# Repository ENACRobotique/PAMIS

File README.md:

# PAMIS_202

Limiter le courant des stepper à 0.6 A

Enlever les solder bridges SB9 SB16 et SB18 de la nucleo L432KC

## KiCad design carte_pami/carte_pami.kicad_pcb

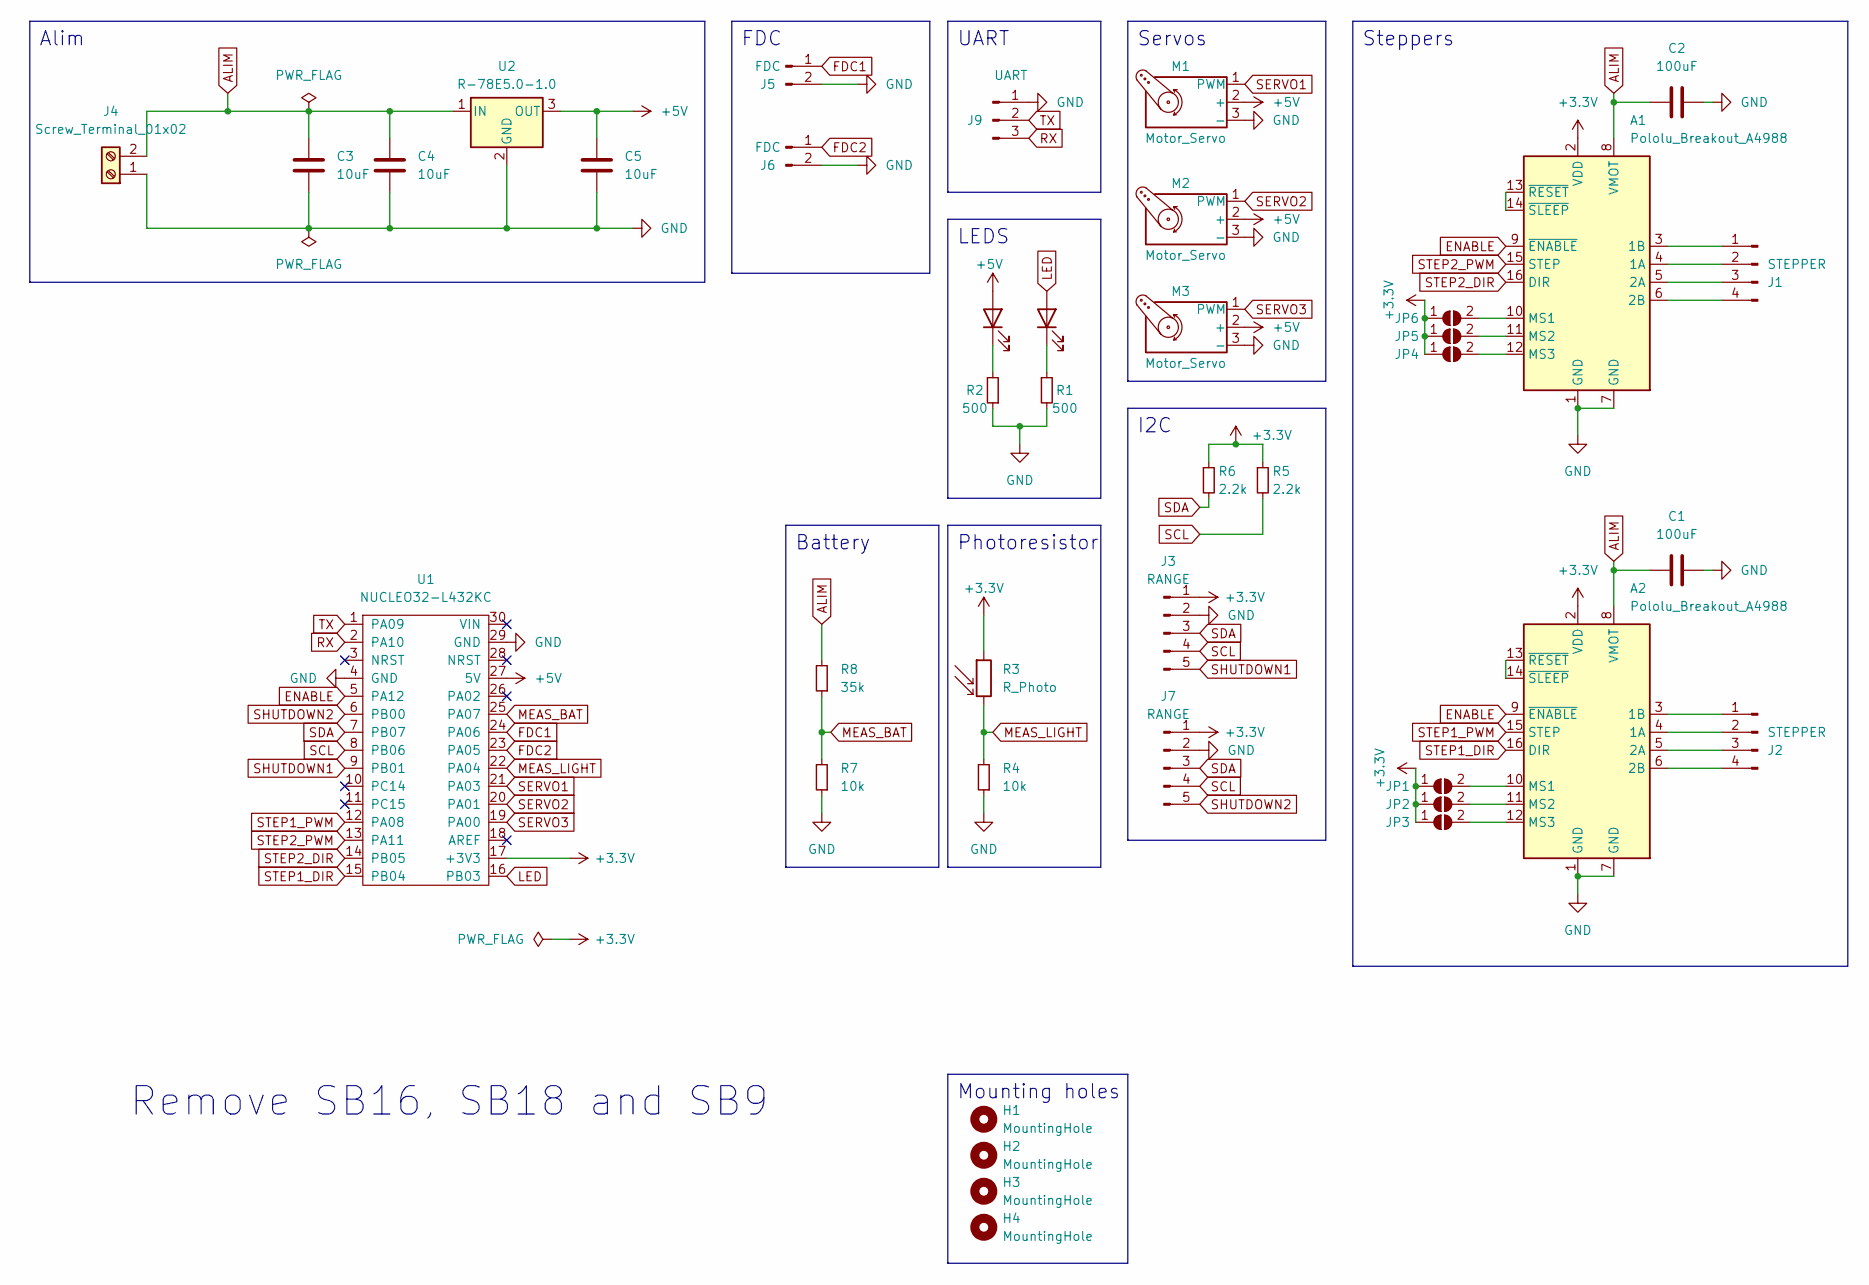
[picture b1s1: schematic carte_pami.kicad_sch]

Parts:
A1, A2: Pololu_Breakout_A4988; Pololu_Breakout-16_15.2x20.3mm
C1, C2: 100uF; CP_Elec_10x12.5
C3, C4, C5: 10uF; C_0805_2012Metric
D1, D2: LED; LED_0603_1608Metric
H1, H2, H3, H4: MountingHole; MountingHole_3.2mm_M3
J1, J2: STEPPER; PinHeader_1x04_P2.54mm_Vertical
J3, J7: RANGE; PinHeader_1x05_P2.54mm_Vertical
J4: Screw_Terminal_01x02; TerminalBlock_bornier-2_P5.08mm
J5, J6: FDC; PinHeader_1x02_P2.54mm_Vertical
J9: UART; PinHeader_1x03_P2.54mm_Vertical
JP1, JP2, JP3, JP4, JP5, JP6: SolderJumper_2_Open; SolderJumper-2_P1.3mm_Open_TrianglePad1.0x1.5mm
M1, M2, M3: Motor_Servo; PinHeader_1x03_P2.54mm_Vertical
R1, R2: 500; R_0805_2012Metric
R3: R_Photo; PinHeader_1x02_P2.54mm_Vertical
R4, R7: 10k; R_0805_2012Metric
R5, R6: 2.2k; R_0805_2012Metric
R8: 35k; R_0805_2012Metric
U1: NUCLEO32-L432KC; NUCLEO32
U2: R-78E5.0-1.0; Converter_DCDC_RECOM_R-78E-0.5_THT

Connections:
+3.3V: A1.2 (VDD), A2.2 (VDD), J3.1, J7.1, JP1.1 (A), JP2.1 (A), JP3.1 (A), JP4.1 (A), JP5.1 (A), JP6.1 (A), R3.1, R5.1, R6.1, U1.17 (+3V3)
+5V: C5.2, D1.2 (A), M1.2 (+), M2.2 (+), M3.2 (+), U1.27 (5V), U2.3 (OUT)
ALIM: A1.8 (VMOT), A2.8 (VMOT), C1.1, C2.1, C3.2, C4.2, J4.2, R8.2, U2.1 (IN)
ENABLE: A1.9 (~ENABLE), A2.9 (~ENABLE), U1.5 (PA12)
FDC1: J5.1, U1.24 (PA06)
FDC2: J6.1, U1.23 (PA05)
GND: A1.1 (GND), A1.7 (GND), A2.1 (GND), A2.7 (GND), C1.2, C2.2, C3.1, C4.1, C5.1, J3.2, J4.1, J5.2, J6.2, J7.2, J9.1, M1.3 (-), M2.3 (-), M3.3 (-), R1.2, R2.1, R4.1, R7.1, U1.4 (GND), U1.29 (GND), U2.2 (GND)
LED: D2.2 (A), U1.16 (PB03)
MEAS_BAT: R7.2, R8.1, U1.25 (PA07)
MEAS_LIGHT: R3.2, R4.2, U1.22 (PA04)
unnamed: A1.4 (1A), J1.2
unnamed: A1.3 (1B), J1.1
unnamed: A1.5 (2A), J1.3
unnamed: A1.6 (2B), J1.4
unnamed: A1.10 (MS1), JP6.2 (B)
unnamed: A1.11 (MS2), JP5.2 (B)
unnamed: A1.12 (MS3), JP4.2 (B)
unnamed: A1.13 (~RESET), A1.14 (~SLEEP)
unnamed: A2.4 (1A), J2.2
unnamed: A2.3 (1B), J2.1
unnamed: A2.5 (2A), J2.3
unnamed: A2.6 (2B), J2.4
unnamed: A2.10 (MS1), JP1.2 (B)
unnamed: A2.11 (MS2), JP2.2 (B)
unnamed: A2.12 (MS3), JP3.2 (B)
unnamed: A2.13 (~RESET), A2.14 (~SLEEP)
unnamed: D1.1 (K), R2.2
unnamed: D2.1 (K), R1.1
RX: J9.3, U1.2 (PA10)
SCL: J3.4, J7.4, R5.2, U1.8 (PB06)
SDA: J3.3, J7.3, R6.2, U1.7 (PB07)
SERVO1: M1.1 (PWM), U1.21 (PA03)
SERVO2: M2.1 (PWM), U1.20 (PA01)
SERVO3: M3.1 (PWM), U1.19 (PA00)
SHUTDOWN1: J3.5, U1.9 (PB01)
SHUTDOWN2: J7.5, U1.6 (PB00)
STEP1_DIR: A2.16 (DIR), U1.15 (PB04)
STEP1_PWM: A2.15 (STEP), U1.12 (PA08)
STEP2_DIR: A1.16 (DIR), U1.14 (PB05)
STEP2_PWM: A1.15 (STEP), U1.13 (PA11)
TX: J9.2, U1.1 (PA09)

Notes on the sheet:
Servos
UART
Photoresistor
Remove SB16, SB18 and SB9
LEDS
FDC
Steppers
I2C
Mounting holes
Alim
Battery

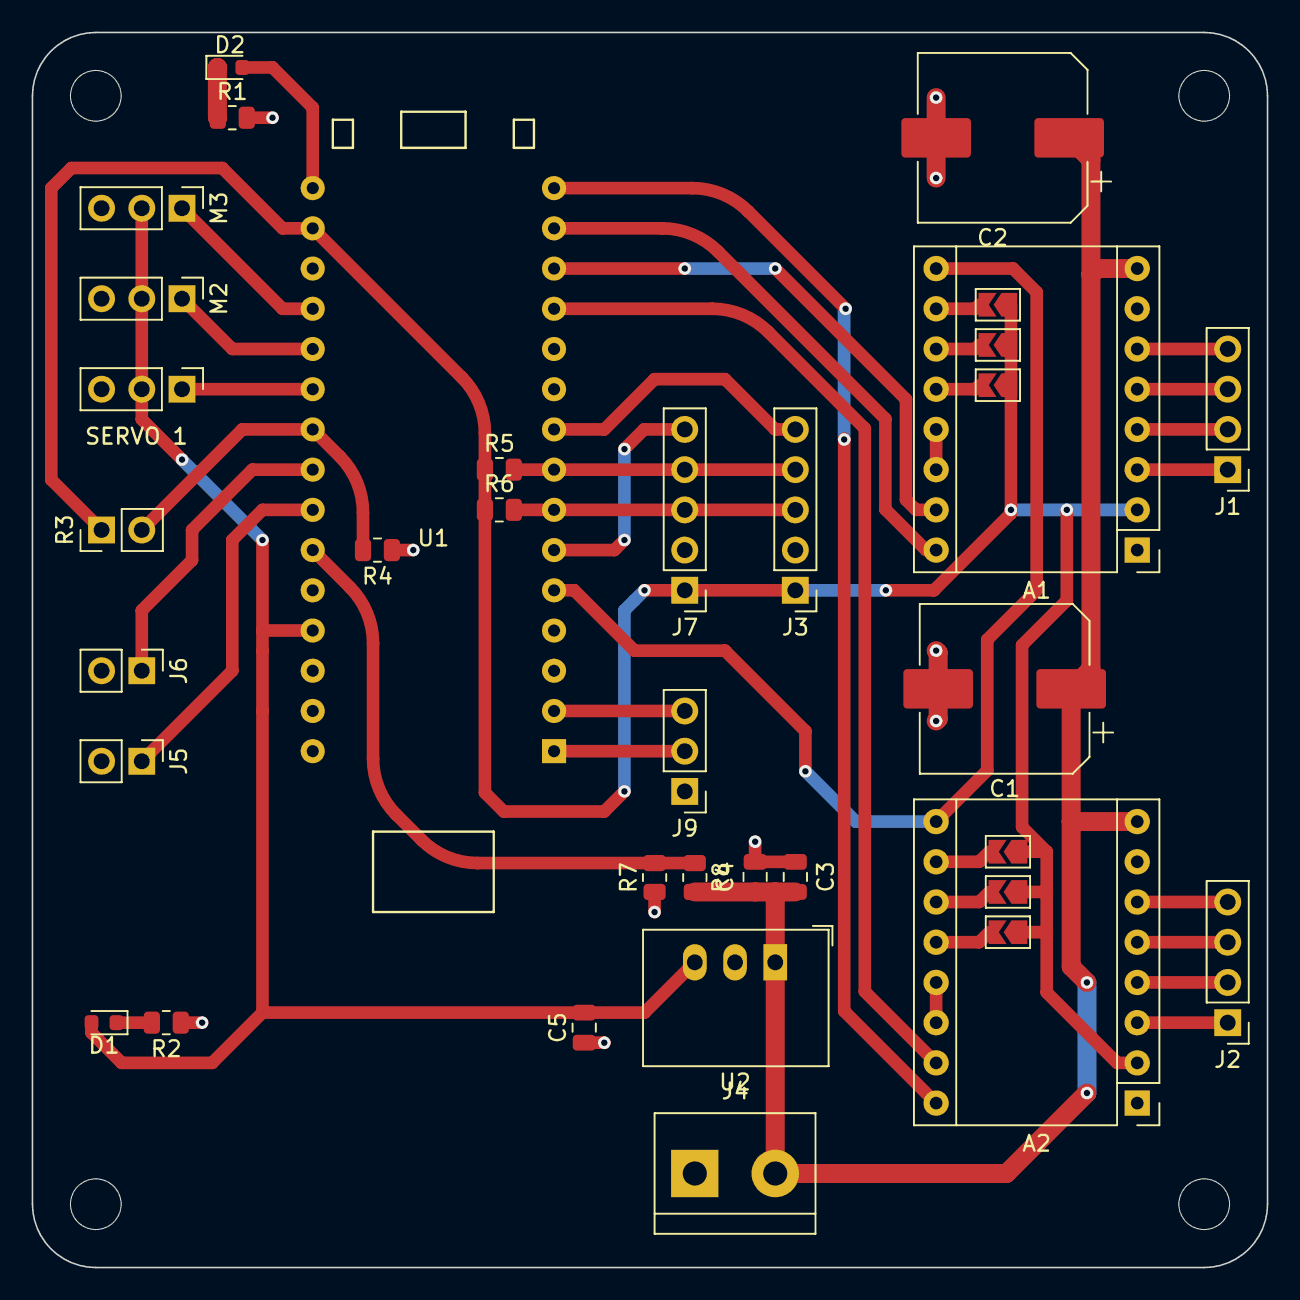
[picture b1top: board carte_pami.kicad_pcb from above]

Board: 2 copper layers, 78.0 x 78.0 mm, 40 parts (0 on the bottom side), 41 nets.

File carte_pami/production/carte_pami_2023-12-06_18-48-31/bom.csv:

Designator,Footprint,Quantity,Value,LCSC Part #
12V,TerminalBlock_bornier-2_P5.08mm,1,Screw_Terminal_01x02,
"C1, C2",CP_Elec_10x12.5,2,100uF,
"C3, C4, C5",0805,3,10uF,
"FDC 1, FDC 2",PinHeader_1x02_P2.54mm_Vertical,2,FDC,
"H1, H2, H3, H4",MountingHole_3.2mm_M3,4,MountingHole,
"J3, J7",PinHeader_1x05_P2.54mm_Vertical,2,RANGE,
"JP1, JP2, JP3, JP4, JP5, JP6",SolderJumper-2_P1.3mm_Open_TrianglePad1.0x1.5mm,6,SolderJumper_2_Open,
"LED 1, LED 2",0603,2,LED,
"M1, M2, M3",PinHeader_1x03_P2.54mm_Vertical,3,Motor_Servo,
PHOTORESISTOR,PinHeader_1x02_P2.54mm_Vertical,1,R_Photo,
"R1, R2",0805,2,500,
"R4, R7",0805,2,10k,
"R5, R6",0805,2,2.2k,
R8,0805,1,35k,
"STEPPER 1_2, STEPPER 2",Pololu_Breakout-16_15.2x20.3mm,2,Pololu_Breakout_A4988,
"STEPPER 1, STEPPER 2_2",PinHeader_1x04_P2.54mm_Vertical,2,STEPPER,
U1,NUCLEO32,1,NUCLEO32-L432KC,
U2,Converter_DCDC_RECOM_R-78E-0.5_THT,1,R-78E5.0-1.0,
UART,PinHeader_1x03_P2.54mm_Vertical,1,UART,

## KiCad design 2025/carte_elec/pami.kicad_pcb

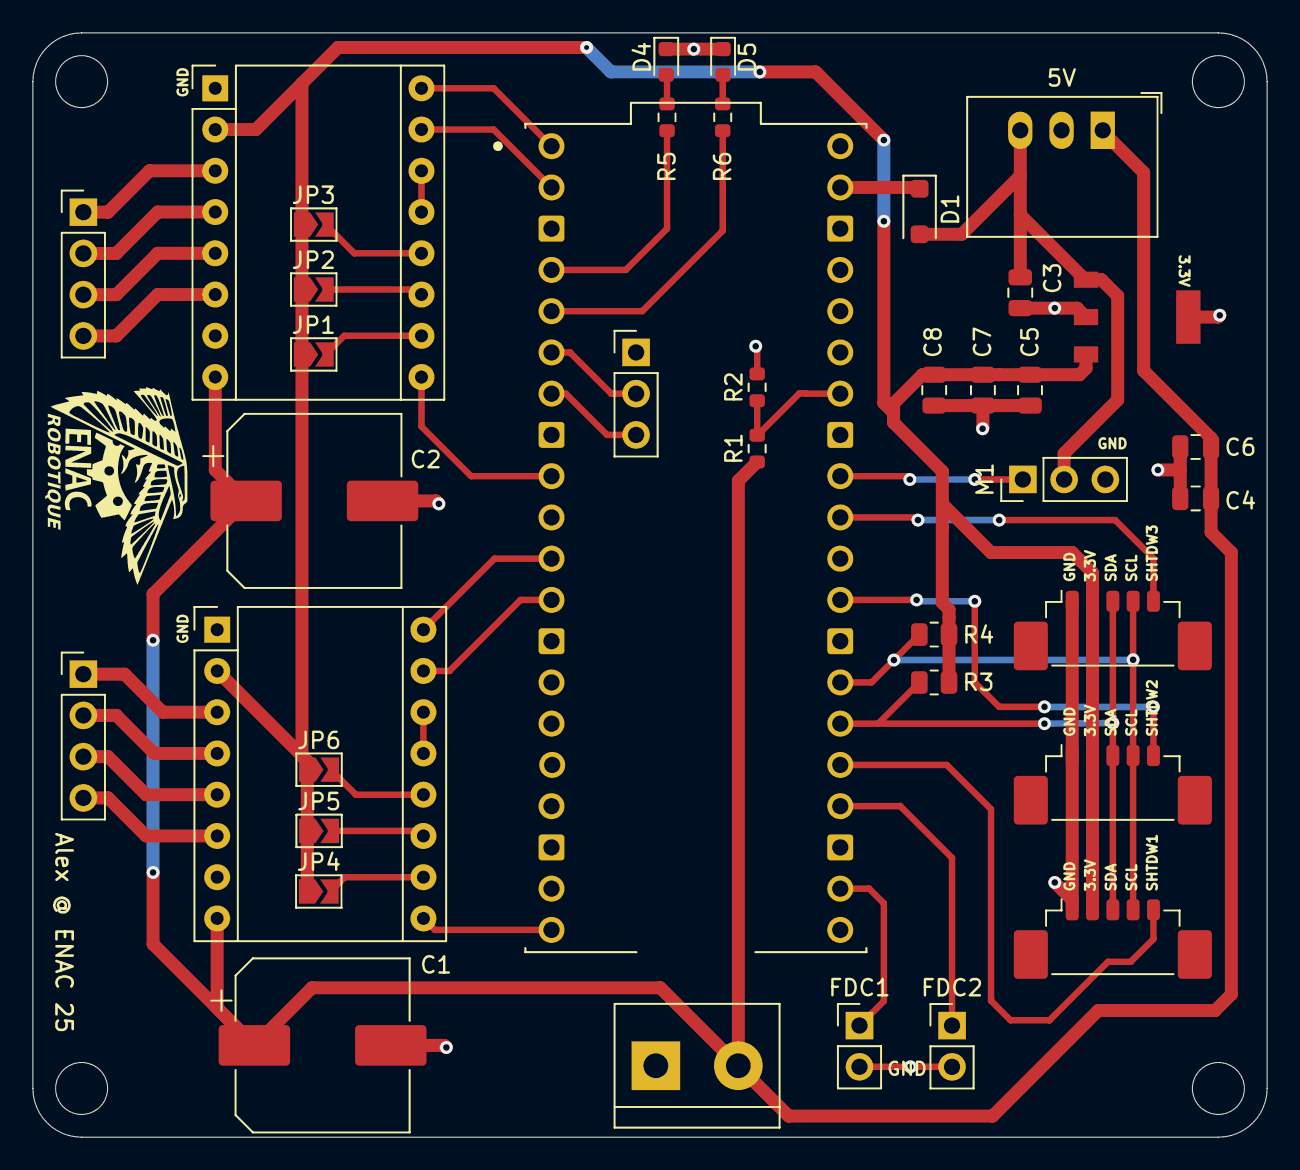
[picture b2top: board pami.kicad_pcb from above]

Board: 2 copper layers, 76.0 x 68.0 mm, 42 parts (0 on the bottom side), 42 nets.

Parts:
5V: R-78E5.0-1.0; Converter_DCDC_RECOM_R-78E-0.5_THT
A1: SC0918; RASPBERRY_PI_PICO
A2, A3: Pololu_Breakout_A4988; Pololu_Breakout-16_15.2x20.3mm
C1, C2: 100uF; CP_Elec_10x12.5
C3: 0.47uF; C_0805_2012Metric
C4, C5, C6, C7, C8: 10uF; C_0805_2012Metric
D1: PMEG2010AEH; D_SOD-123F
D4, D5: LED; LED_0603_1608Metric
FDC1, FDC2: FDC; PinHeader_1x02_P2.54mm_Vertical
H1, H2, H3, H4: MountingHole; MountingHole_3.2mm_M3
IC1: LM3940IMP-3.3; LM3940IMP
J1, J2: STEPPER; PinHeader_1x04_P2.54mm_Vertical
J3: UART; PinHeader_1x03_P2.54mm_Vertical
J4, J5, J9: RANGE; Molex_PicoBlade_53398-0571_1x05-1MP_P1.25mm_Vertical
J8: Screw_Terminal_01x02; TerminalBlock_bornier-2_P5.08mm
JP1, JP2, JP3, JP4, JP5, JP6: SolderJumper_2_Open; SolderJumper-2_P1.3mm_Open_TrianglePad1.0x1.5mm
M1: Motor_Servo; PinHeader_1x03_P2.54mm_Vertical
R1: 18k; R_0603_1608Metric
R2: 8.2k; R_0603_1608Metric
R3, R4: 2.2k; R_0805_2012Metric
R5, R6: 470; R_0603_1608Metric

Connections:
+3.3V: A2.2 (VDD), A3.2 (VDD), C5.1, C7.1, C8.1, IC1.3 (OUT), J4.2, J5.2, J9.2, JP1.1 (A), JP2.1 (A), JP3.1 (A), JP4.1 (A), JP5.1 (A), JP6.1 (A), R3.1, R4.1
+5V: 5V.3 (OUT), C3.1, D1.2 (A), IC1.1 (IN), M1.2 (+)
+BATT: 5V.1 (IN), A2.8 (VMOT), A3.8 (VMOT), C1.1, C2.1, C4.2, C6.2, J8.2, R1.1
BAT_MESURE: A1.34 (GP28), R1.2, R2.1
ENABLE1: A1.9 (GP6), A3.9 (~ENABLE)
ENABLE2: A1.20 (GP15), A2.9 (~ENABLE)
FDC1: A1.22 (GP17), FDC1.1
FDC2: A1.24 (GP18), FDC2.1
GND: 5V.2 (GND), A1.3 (GND), A1.8 (GND), A1.13 (GND), A1.18 (GND), A1.23 (GND), A1.28 (GND), A1.33 (AGND), A1.38 (GND), A2.1 (GND), A2.7 (GND), A3.1 (GND), A3.7 (GND), C1.2, C2.2, C3.2, C4.1, C5.2, C6.1, C7.2, C8.2, D4.1 (K), D5.1 (K), FDC1.2, FDC2.2, IC1.2 (GND), IC1.4 (TAB), J3.1, J4.1, J5.1, J8.1, J9.1, M1.3 (-), R2.2
LED1: A1.4 (GP2), R5.2
LED2: A1.5 (GP3), R6.2
unnamed: A1.39 (VSYS), D1.1 (K)
unnamed: A2.4 (1A), J1.2
unnamed: A2.3 (1B), J1.1
unnamed: A2.5 (2A), J1.3
unnamed: A2.6 (2B), J1.4
unnamed: A2.10 (MS1), JP4.2 (B)
unnamed: A2.11 (MS2), JP5.2 (B)
unnamed: A2.12 (MS3), JP6.2 (B)
unnamed: A2.13 (~RESET), A2.14 (~SLEEP)
unnamed: A3.4 (1A), J2.2
unnamed: A3.3 (1B), J2.1
unnamed: A3.5 (2A), J2.3
unnamed: A3.6 (2B), J2.4
unnamed: A3.10 (MS1), JP1.2 (B)
unnamed: A3.11 (MS2), JP2.2 (B)
unnamed: A3.12 (MS3), JP3.2 (B)
unnamed: A3.13 (~RESET), A3.14 (~SLEEP)
unnamed: D4.2 (A), R5.1
unnamed: D5.2 (A), R6.1
RX: A1.7 (GP5), J3.3
SCL: A1.27 (GP21), J4.4, J5.4, J9.4, R4.2
SDA: A1.26 (GP20), J4.3, J5.3, J9.3, R3.2
SERVO: A1.32 (GP27), M1.1 (PWM)
SHUTDOWN1: A1.25 (GP19), J5.5
SHUTDOWN2: A1.29 (GP22), J4.5
SHUTDOWN3: A1.31 (GP26), J9.5
STEP1_DIR: A1.1 (GP0), A3.16 (DIR)
STEP1_PWM: A1.2 (GP1), A3.15 (STEP)
STEP2_DIR: A1.11 (GP8), A2.16 (DIR)
STEP2_PWM: A1.12 (GP9), A2.15 (STEP)
TX: A1.6 (GP4), J3.2

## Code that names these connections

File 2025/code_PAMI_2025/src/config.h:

#pragma once

// // #define BOWIE
//#define STEVE
#define JOHNNY
//#define JIMMY

#define DISTANCEEVITEMENT 100
#define DISTANCEEVITEMENT_JHONNY 100

#undef LED1
#define LED1 2

#undef LED2
#define LED2 3

#define UARTTX 4
#define UARTRX 5

#define ENABLE2 15
#define DIR2 8
#define STEP2 9

#define ENABLE1 6
#define DIR1 0
#define STEP1 1

#define FDC1 17
#define FDC2 18

#define SHUTDOWN1 19
#define SHUTDOWN2 22
#define SHUTDOWN3 26
#define SDA 20
#define SCL 21

#define SERVO 27

#define BAT_MESURE 28

#define TIRETTE FDC2

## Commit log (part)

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2023-11-09 Start elec board.
2023-11-16 update carte en cours
2023-11-23 schematique pami
2023-11-23 placement composantes
2023-11-25 Petits ajouts au schéma, et définition des capabilities.
2023-11-25 routage by Fab
2023-11-26 JPO test. Pour la carte "IO board 2022" de Fab@RustyDucks.
2023-11-29 setup right stepper
2023-11-29 avance et tourne
2023-11-29 Classe pilotage mais sans odom
2023-11-30 commande de déplacement ok
2023-11-30 petit pami fait des rond !
2023-12-01 mesure batterie
2023-12-05 routage
2023-12-06 fini le routage de la carte
2023-12-07 classes
2023-12-21 capteur distance ok
2024-02-01 plus de gpios
2024-02-01 double capteurs
2024-02-04 le robot se deplace de points en point
2024-02-08 evitement
2024-02-09 odometry
2024-02-09 evitement qui fonctionne et suivi de trajectoire
2024-02-15 adapter pour la nouvelle L432KC
2024-02-16 ommission des points de passage et départ avec photoresistance
2024-02-28 signal recu du capteur central
2024-02-29 capteur milieu efficace pour evitement + trajectoire pour nouveau robot + initialisation coord
2024-02-29 Mesure tension batterie et buzzer.
2024-02-29 réglages PCB
2024-03-21 deploiement godet
2024-04-26 les VL53L0X sont dans le bon sens
2024-04-27 choix de la stratégie selon l'équipe, ajout du non arret au dernier point, detection grace à la led de l'UCD
2024-04-27 UCD Qui marche
2024-05-03 UCD again
2024-05-07 adaptation 3 PAMIS avec différents capteurs
2024-05-08 adapt for all pamis
2024-05-13 code coupe
2024-05-23 milo wait 4 sec
2024-07-03 vision a part + demarrage au moment ou l'on eclaire la photoresistance
2024-07-04 creation Vtask mouvement
2024-09-04 code coupe avec freertos
2024-09-10 for presentation
2024-09-10 random angle + minor bug fix)
2024-09-13 remove levier
2024-09-13 carre + vision ok
2024-09-13 rangement du tuto dans un fichier à part
2024-10-13 cactus
2025-02-17 organisation par année
2025-02-17 pamis 2025
2025-02-18 include extern
2025-02-19 projet 2025 pami platformio
2025-02-19 test steppers
2025-02-19 Pico: meilleure plateform.
2025-02-19 Commence locomotion.
2025-02-19 [VL53L1x] Importe library ST.
2025-02-21 Radar
2025-03-24 add odometry + rotate_blocking
2025-03-24 mise a jour odom + debut de fonction move (qui marche pas attention
2025-04-02 move target + resolve bug convert Step2MM
2025-04-02 peut aller de point en point, pour n points
2025-04-03 avoiding maneouver in progress
2025-04-07 avoid in progress (non fonctionnel)
2025-04-10 (angle opti + radar stupide) done
2025-04-15 suivi des murs fonctionnel
2025-04-17 esquives 30° et 90° et suivi lignes marchent 80% du temps
2025-04-24 suiviLignes fixed wrong side when following right to left wall
2025-05-19 accel des pamis + augmentation lisibilité
2025-05-21 FDC done, 15 seconds done
2025-05-22 tirette delay added +startpos
2025-05-23 fixed suivilignes
2025-05-25 [superstar] all work excecpt evitement
2025-05-26 better avoidance + parkour
2025-05-27 bras added
2025-05-27 cancel esquive quand dans zone finale
2025-05-28 [everything] Match complet réalisé (evitement non satisfaisant)
2025-05-28 ajustement
2025-05-28 [evitement] freinage plus fort
2025-05-29 [superstar] réglage vitesse superstar
2025-05-29 johnny may go without avoiding partners
2025-05-29 [superstar] adaptation montée
2025-05-29 remove Bowie et changement cible des zones pamis
2025-05-29 nouvelle coord pamis pour coupe + steve dans le code correspond a bowie dans la vrai vie
2025-05-29 reduction evitement superstar
2025-10-08 tests
2026-01-16 Starts PAMI 2026
2026-01-20 begin steppers + convert to C++
2026-01-20 flash with UART
2026-01-21 Fixed-point arithmetics for steppers
2026-01-22 Begin Web server
2026-01-22 add sdkconfig
2026-01-23 Revert "add sdkconfig"
    This reverts commit b5591d5a5518f47b6ce4f6e7c1d816b989d8274c.
2026-01-23 KConfig default values
2026-01-24 Fallback WiFi AP + page web
2026-01-26 Template odometry
2026-01-26 start IMU
2026-02-02 add odometry
2026-02-03 remove test à la con
2026-02-03 add trajectories fundations
2026-02-03 fix odometry
2026-02-06 added movement state
2026-02-17 Working trajectory
2026-02-18 VL53L1X fonctionne !
2026-02-24 multi radar
2026-02-24 radar refactor
2026-02-24 enable IMU back
2026-02-25 organize files and clean main code
2026-02-25 make teleplot server configurable
2026-03-04 start protobuf tests
2026-03-04 vl53 get distance
2026-03-04 STS3032 move
2026-03-06 sts3032 readPos
2026-03-31 Update locomotion move : Trajectoire courbe
2026-04-07 [locomotion et main] wallid_sortir_caisse
2026-04-11 finir_strat_wallid_v1
2026-04-13 wallid_mission_entiere_1
2026-04-13 strat_entiere_wallid_2
2026-04-14 walklid_nouvezlle_roue
2026-04-17 do not use proto for now
2026-04-17 [SAP] ping
2026-04-17 strat
2026-04-17 check SAP init OK
2026-04-17 Strat fondation
2026-05-04 Rajout de la fonction stop slow sur le stepper
2026-05-04 Modification de la fonction stop
2026-05-06 wallidTeam
2026-05-07 tirette_fin_equipe_et_stratWallid_cree
2026-05-08 Changement des numéros de robot + start ecurueil
2026-05-08 séparation strat grenier
2026-05-08 changement strat.h
2026-05-08 correction de bug apres merge
2026-05-08 initilisation UART + correction vitesse steppeur
2026-05-08 arrangement_strat_wallid_1
2026-05-10 Odometrie main + chanegement teleplot html
2026-05-11 séparation strat et nom mémoire HTML
2026-05-11 htlm+ modif accel et frein
2026-05-11 fin wallid
2026-05-11 correctoion_legere
2026-05-11 scs009 strat 1 2 3 pami ecureuil
2026-05-12 mardi soir, details wallid
2026-05-12 queue bougeant fin de match + trajectoire fini (reste a faire évitement annulé pour le PAMI4 qui pousse + tester de lancer les 4 en mm temps)
2026-05-13 pamiçamarche
2026-05-13 mis a jout temps d'attente
2026-05-13 changment de la distance pour homologation
